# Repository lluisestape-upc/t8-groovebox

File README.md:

# T-8 Groovebox

A 16-step hardware groovebox built around an ESP32-WROOM-32, designed from scratch in KiCad 10. Two copper layers, 290 × 210 mm, DRC-clean and fabrication-ready.

> **Status: designed, not yet fabricated.**
> The layout passes DRC with **0 errors and 0 unconnected nets**, and the Gerber + drill package in [`fab/`](fab/) has been generated and checked. No board has been ordered yet, so nothing here has been measured on real hardware. Every performance figure in this README is a design intent, not a measurement.

---

## What it is

A desktop groovebox in the spirit of the Roland T-8: sixteen step buttons with per-step RGB feedback, ten pots for live parameter control, a rotary encoder for menu navigation, a 2.4" colour display, MIDI in and out over TRS-A, and two independent audio outputs — a line-level I²S DAC and a class-D amplifier for a small onboard speaker. The whole thing is powered and programmed over a single USB-C connector.

The interesting part of this project is not the feature list, it is that the panel layout and most of the routing were **generated and repaired with the KiCad Python API** rather than drawn by hand. See [How the board was built](#how-the-board-was-built).

## Board at a glance

| | |
|---|---|
| Outline | 290.1 × 210.1 mm, with a 7 mm notch for the MIDI jacks |
| Copper layers | 2 (F.Cu / B.Cu), 1 oz |
| Footprints | 104 |
| Pads | 523 |
| Nets | 137 |
| Tracks | 2,570 segments |
| Vias | 1,148 (0.6 mm pad / 0.3 mm drill) |
| Copper zones | 1 GND plane, poured on both layers |
| Min track / clearance | 0.20 mm / 0.20 mm |
| Min drill | 0.30 mm |
| Min copper-to-edge | 0.50 mm |
| Mounting | 6 × M3 (3.2 mm) |
| DRC | 0 errors, 0 unconnected, 12 cosmetic silkscreen warnings |

### Renders

| Top | Bottom |
|---|---|
|  |  |

Vector fabrication views: [top](img/t8_2d_top.svg) · [bottom](img/t8_2d_bottom.svg)

PDFs: [schematic](T8Sequencer_esquematico.pdf) · [PCB](T8Sequencer_pcb.pdf)

---

## Signal chain

```mermaid
flowchart LR
  USB["USB-C J1"] --> UART["CH340C USB-UART"]
  USB --> LDO["AMS1117-3.3"]
  UART -->|UART0| ESP["ESP32-WROOM-32"]
  UART -.->|DTR / RTS via Q1, Q2| ESP
  LDO -->|3.3 V| ESP

  STEPS["16 step buttons"] --> EXP1["MCP23017 0x20"]
  FNKEYS["8 function buttons"] --> EXP2["MCP23017 0x21"]
  EXP1 -->|I2C| ESP
  EXP2 -->|I2C| ESP
  POTS["10 potentiometers"] --> MUX["CD74HC4067 16:1 mux"]
  MUX -->|ADC on GPIO34| ESP
  ENC["Rotary encoder + switch"] --> ESP

  ESP -->|GPIO16| LVL["74AHCT1G125 level shifter"]
  LVL -->|33 ohm series| LEDS["16x WS2812B"]
  ESP -->|SPI| DISP["ST7789 2.4in module"]
  ESP -->|I2S| DAC["I2S DAC header, line out"]
  ESP -->|I2S| AMP["MAX98357A module, speaker"]
  ESP -->|GPIO32| MOUT["MIDI OUT TRS-A, J3"]
  MIDIIN["MIDI IN TRS-A, J2"] --> OPTO["6N138 optocoupler"]
  OPTO -->|GPIO17| ESP
```

---

## Hardware

### Controls and indicators

| Qty | Part | Role |
|---|---|---|
| 16 | 6 mm tact switch | Step buttons (SW1–SW16) |
| 8 | 6 mm tact switch | PLAY, REC, SHIFT, PATT, TEMPO, CLEAR, F1, F2 (SW17–SW24) |
| 10 | Alps RK09K vertical | Parameter pots (RV1–RV10) |
| 1 | Alps EC11E + switch | Menu encoder |
| 16 | WS2812B (PLCC-4, 5×5 mm) | Per-step RGB feedback |
| 1 | ST7789 2.4" module | Display, on an 8-pin 2.54 mm header |

### Active devices

| Ref | Part | Package | Role |
|---|---|---|---|
| U1 | ESP32-WROOM-32 | module | Main MCU |
| U2 | — | 1×06 header | I²S DAC module, line out |
| U3 | ST7789 2.4" | 1×08 header | Display |
| U4 | CD74HC4067M | SOIC-24W | 16:1 analog mux for the pots |
| U5 | AMS1117-3.3 | SOT-223 | 3.3 V linear regulator |
| U6 | CH340C | SOIC-16 | USB to serial |
| U7 | MCP23017 | DIP-28 | I/O expander, step buttons (0x20) |
| U8 | 6N138 | DIP-8 | MIDI IN isolation |
| U9 | MAX98357A | 1×07 header | Class-D amp module, speaker out |
| U10 | MCP23017 | DIP-28 | I/O expander, function buttons (0x21) |
| U11 | 74AHCT1G125 | SOT-23-5 | 3.3 V to 5 V buffer for the LED data line |
| Q1, Q2 | NPN | SOT-23 | Auto-reset (DTR/RTS to EN/IO0) |

### Connectors

| Ref | Connector | Notes |
|---|---|---|
| J1 | USB-C receptacle, USB 2.0 14P | Power + programming, with 5.1 kΩ CC pulldowns |
| J2 | 3.5 mm TRS | MIDI IN, **TRS-A** (tip = DIN 5, ring = DIN 4) |
| J3 | 3.5 mm TRS | MIDI OUT, **TRS-A** |

Audio leaves the board through the connectors on the DAC and amplifier modules, not through board-mounted jacks.

---

## ESP32 pin map

| GPIO | Net | Function |
|---|---|---|
| 0 | `ESP_IO0` | Boot strap, driven by Q2 from RTS |
| 1 / 3 | `TX` / `RX` | UART0 to the CH340C |
| 2 | `DC` | Display data/command |
| 4 | `RES` | Display reset |
| 5 | `TFT_CS` | Display chip select |
| 12 | `MUX_S0` | Mux select bit 0 |
| 13 | `MUX_S1` | Mux select bit 1 |
| 14 | `MUX_S2` | Mux select bit 2 |
| 15 | `DISP_MOSI` | Display data |
| 16 | `LED_DATA` | WS2812B chain, via the 74AHCT1G125 |
| 17 | `MIDI_RX` | MIDI IN, from the 6N138 |
| 18 | `SCL` | I²C clock |
| 19 | `ENC_A` | Encoder channel A |
| 21 | `ENC_B` | Encoder channel B |
| 22 | `I2S_DIN` | I²S data out, shared by both audio devices |
| 23 | `SDA` | I²C data |
| 25 | `I2S_LCK` | I²S word clock |
| 26 | `I2S_BCK` | I²S bit clock |
| 27 | `MUX_S3` | Mux select bit 3 |
| 32 | `MIDI_TX` | MIDI OUT |
| 33 | `DISP_SCK` | Display clock |
| 34 | `MUX_SIG` | Pot mux output to ADC (input-only pin) |
| 35 | `ENC_SW` | Encoder push switch (input-only pin) |
| EN | `ESP_EN` | Reset, driven by Q1 from DTR |

`GPIO34` and `GPIO35` are input-only on the ESP32, which is exactly how they are used here. `GPIO12` is a boot strapping pin (MTDI); it is driven as a mux select with no external pull, so nothing holds it high at reset, but it is worth keeping in mind when writing the firmware.

## I²C and mux map

Both expanders share `SDA`/`SCL` with `RESET` tied to 3.3 V. Buttons pull to ground, so enable the internal pull-ups (`GPPU`).

| Device | Address | Port A | Port B |
|---|---|---|---|
| U7 | `0x20` | steps 1–8 | steps 9–16 |
| U10 | `0x21` | PLAY, REC, SHIFT, PATT, TEMPO, CLEAR, F1, F2 | free (8 spare inputs) |

The CD74HC4067 uses 10 of its 16 channels (`POT0`–`POT9`), selected by `MUX_S0..S3`, with the common pin read on `GPIO34`. Allow for RC settling between the channel switch and the ADC read.

The WS2812B chain is wired as a serpentine, not in reference order:

```
D1 → D2 → D3 → D4 → D5 → D10 → D11 → D12 → D6 → D7 → D8 → D9 → D14 → D15 → D16 → D17
```

Firmware has to map logical step *n* onto this physical order.

---

## Fabrication

[`fab/`](fab/) holds the complete package, also zipped as [`T8Sequencer_fab.zip`](T8Sequencer_fab.zip):

- 7 Gerbers — F.Cu, B.Cu, F.Mask, B.Mask, F.Silkscreen, B.Silkscreen, Edge.Cuts
- Excellon drill files, split PTH / NPTH
- `.gbrjob` job file

Settings the design was checked against:

| Setting | Value | Why |
|---|---|---|
| Layers | 2 | |
| Thickness | 1.6 mm | |
| Copper weight | 1 oz | 2 oz would raise the headroom of the 0.2 mm tracks from ≈0.74 A to ≈1.2 A, at higher cost |
| Min hole size | **0.3 mm** | 0.2 mm crosses into a much more expensive price tier |
| Min track / spacing | 0.2 mm / 0.2 mm | |
| Surface finish | HASL | |

The ESP32 thermal vias were deliberately enlarged from 0.2 mm to 0.3 mm drill (0.7 mm pad) purely to stay under the cheaper drill tier.

---

## Repository layout

```
T8Sequencer.kicad_pro          project
T8Sequencer.kicad_sch          schematic (single sheet)
T8Sequencer.kicad_pcb          layout
T8Sequencer.xml                netlist export
fp-lib-table                   project footprint libraries
sin_marco.kicad_wks            borderless worksheet, for clean plots
lib/Lluis.kicad_sym            custom symbols (module headers)
Lluis.pretty/                  custom footprints
LCD ST7789V.pretty/            the original FPC display footprint (superseded)
fab/                           Gerbers + drill
img/                           3D renders and 2D fabrication views
build_pcb.py                   board bring-up script
place_panel.py                 panel placement generator
scripts_arreglo/               the repair scripts, in the order they were run
```

### Opening the project

The schematic depends on the custom symbol library in `lib/Lluis.kicad_sym`, which is **not** registered by a project-level `sym-lib-table`. Add it once under *Preferences → Manage Symbol Libraries* with the nickname `Lluis`, or point an existing entry at the copy in `lib/`. The footprint libraries resolve automatically through `fp-lib-table`.

---

## How the board was built

The panel is a grid of 16 switches, 16 LEDs and 10 pots. Placing that by hand is tedious and error-prone, so the geometry is generated instead:

- **`place_panel.py`** computes the panel grid and writes footprint positions straight into the board.
- **`build_pcb.py`** handles board-level bring-up.
- **`scripts_arreglo/`** holds the repair passes in the order they were run — `fix1`–`fix9`, `fix11`, `fix12` for connectivity and geometry, `ruta`–`ruta4` for routing, `esq` for the schematic. Each one is a single, auditable change.

Two problems in there are worth reading if you ever script KiCad.

**Duplicate-numbered pads.** 73 pads in this design share a number with another pad in the same footprint — tact switches with two pads numbered 1 and two numbered 2, the USB-C shield with four `SH` pads, the ESP32 thermal pad split into eight. The netlist assigns a net to *one* of them, so the rest stay at net 0 and the copper never connects. Neither ERC nor the netlist reveals this. The fix walks every footprint, groups pads by number, and propagates the single non-zero net to its twins:

```python
byn = collections.defaultdict(list)
for p in f.Pads():
    byn[p.GetNumber()].append(p)
for num, ps in byn.items():
    nets = {p.GetNetCode() for p in ps if p.GetNetCode() != 0}
    if len(nets) == 1 and any(p.GetNetCode() == 0 for p in ps):
        net = B.FindNet(nets.pop())
        for p in ps:
            if p.GetNetCode() == 0:
                p.SetNet(net)
```

**`GetTracks()` is invalidated by `Remove()`.** Iterating the track list while deleting from it segfaults the interpreter. Collect first, delete afterwards:

```python
fuera = [t for t in B.GetTracks() if condicion(t)]
for t in fuera:
    B.Remove(t)
```

---

## Design notes and open risks

Written down plainly, because none of it has been measured yet.

**The 3.3 V regulator is the hot spot.** The AMS1117 drops 5 V to 3.3 V linearly, so it burns 1.7 V times whatever the rail draws:

| 3.3 V load | Dissipation | Rise over ambient (SOT-223) |
|---|---|---|
| 300 mA | 0.51 W | ≈40 °C |
| 500 mA | 0.85 W | ≈65 °C |
| 800 mA | 1.36 W | too much |

Quiescent operation is fine. With Wi-Fi transmitting (peaks around 500 mA) plus the display backlight, the package gets hot. This is the first thing to measure on a real board, and the obvious upgrade is a buck converter.

**The LED ring can outdraw a USB port.** 16 WS2812B at full white is roughly 960 mA on the 5 V rail, against the 500 mA a plain USB 2.0 port guarantees. Cap the brightness in firmware.

**Every track sits at the 0.2 mm minimum.** That is ≈0.74 A at 1 oz by IPC-2221 — adequate for the logic rails, with no margin on the 5 V LED rail. Widening the power tracks was attempted and produced 138+ clearance errors: the routing is dense enough that it needs manual rework, or 2 oz copper, or both.

**Three module pinouts are assumed, not verified.** The display (U3), the DAC (U2) and the amplifier (U9) are all 2.54 mm headers, and the pin order was taken from the common breakout variants. **Check the silkscreen on the parts you actually buy against the schematic before soldering.** The schematic carries a note to this effect on U9.

**12 silkscreen warnings remain.** Reference text on J2 and J3 overhangs the board edge near the MIDI notch. Cosmetic only, no effect on fabrication.

---

## Next steps

- [ ] Order the boards (1 oz, min hole 0.3 mm)
- [ ] Buy the 8-pin 2.4" ST7789 module and verify its pin order
- [ ] Verify the MAX98357A and I²S DAC module pinouts
- [ ] Prototype the firmware in simulation before the boards arrive
- [ ] Bring-up: power rails, regulator temperature, USB enumeration, auto-reset
- [ ] Characterise: line-out THD+N and noise floor, I²S end-to-end latency, MIDI TRS jitter, LED current against brightness
- [ ] Add silkscreen function labels for the pots and step buttons

---

## License

MIT — see [LICENSE](LICENSE).

Designed by [Lluís Estapé](https://github.com/lluisestape-upc). KiCad 10.0.1.

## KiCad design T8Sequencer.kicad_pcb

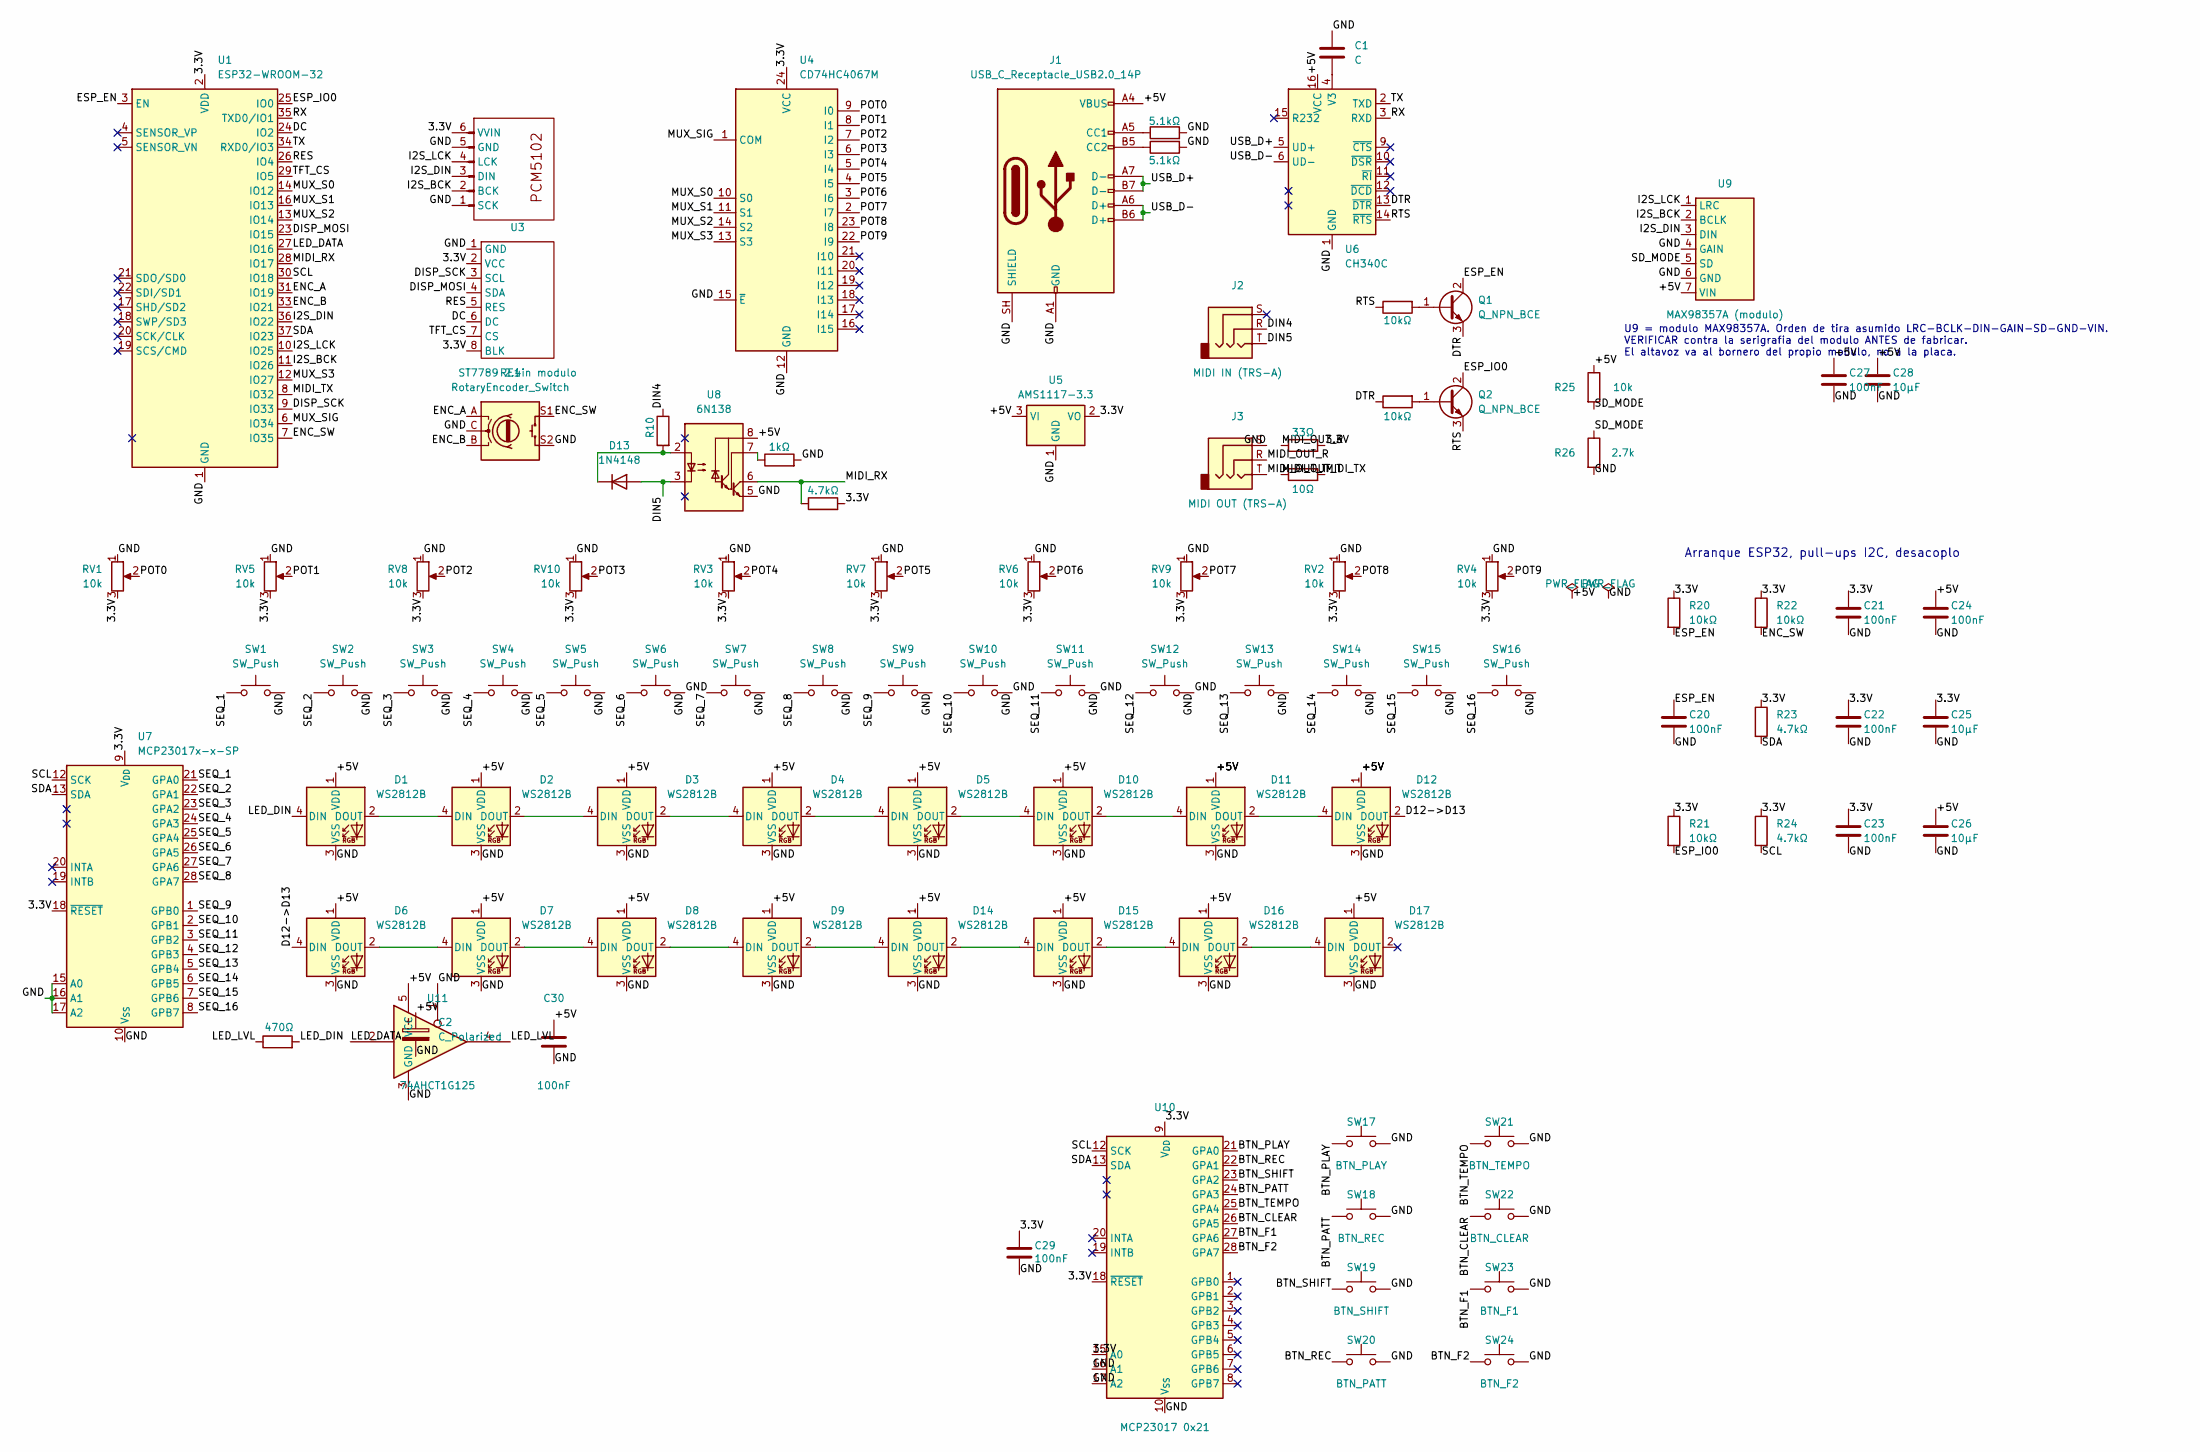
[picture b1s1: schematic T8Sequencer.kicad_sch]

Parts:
C1: C; C_0805_2012Metric
C2: C_Polarized; CP_Radial_D10.0mm_P5.00mm
C20, C21, C22, C23, C24, C27, C29, C30: 100nF; C_0805_2012Metric
C25, C26, C28: 10µF; C_0805_2012Metric
D1, D2, D3, D4, D5, D6, D7, D8, D9, D10, D11, D12, D14, D15, D16, D17: WS2812B; LED_WS2812B_PLCC4_5.0x5.0mm_P3.2mm
D13: 1N4148; D_DO-35_SOD27_P7.62mm_Horizontal
J1: USB_C_Receptacle_USB2.0_14P; USB_C_Receptacle_HRO_TYPE-C-31-M-12
J2: MIDI IN (TRS-A); Jack_3.5mm_CUI_SJ1-3523N_Horizontal
J3: MIDI OUT (TRS-A); Jack_3.5mm_CUI_SJ1-3523N_Horizontal
Q1, Q2: Q_NPN_BCE; SOT-23
R1, R2: 5.1kΩ; R_0805_2012Metric
R3, R4, R20, R21, R22: 10kΩ; R_0805_2012Metric
R5: 470Ω; R_0805_2012Metric
R6: 1kΩ; R_0805_2012Metric
R7, R23, R24: 4.7kΩ; R_0805_2012Metric
R8: 33Ω; R_0805_2012Metric
R9: 10Ω; R_0805_2012Metric
R10: 220; R_0805_2012Metric
R25: 10k; R_0805_2012Metric
R26: 2.7k; R_0805_2012Metric
RE1: RotaryEncoder_Switch; RotaryEncoder_Alps_EC11E-Switch_Vertical_H20mm
RV1, RV2, RV3, RV4, RV5, RV6, RV7, RV8, RV9, RV10: 10k; Potentiometer_Alps_RK09K_Single_Vertical
SW1, SW2, SW3, SW4, SW5, SW6, SW7, SW8, SW9, SW10, SW11, SW12, SW13, SW14, SW15, SW16: SW_Push; SW_PUSH_6mm
SW17: BTN_PLAY; SW_PUSH_6mm
SW18: BTN_REC; SW_PUSH_6mm
SW19: BTN_SHIFT; SW_PUSH_6mm
SW20: BTN_PATT; SW_PUSH_6mm
SW21: BTN_TEMPO; SW_PUSH_6mm
SW22: BTN_CLEAR; SW_PUSH_6mm
SW23: BTN_F1; SW_PUSH_6mm
SW24: BTN_F2; SW_PUSH_6mm
U1: ESP32-WROOM-32
U2: PinHeader_1x06_P2.54mm_Vertical
U3: ST7789 2.4in modulo; PinHeader_1x08_P2.54mm_Vertical
U4: CD74HC4067M; SOIC-24W_7.5x15.4mm_P1.27mm
U5: AMS1117-3.3; SOT-223-3_TabPin2
U6: CH340C; SOIC-16_3.9x9.9mm_P1.27mm
U7: MCP23017x-x-SP; DIP-28_W7.62mm
U8: 6N138; DIP-8_W7.62mm
U9: MAX98357A (modulo); PinHeader_1x07_P2.54mm_Vertical
U10: MCP23017 0x21; DIP-28_W7.62mm
U11: 74AHCT1G125; SOT-23-5

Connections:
/3.3V: C21.1, C22.1, C23.1, C25.1, C29.1, R7.2, R8.2, R20.1, R21.1, R22.1, R23.1, R24.1, RV1.3, RV2.3, RV3.3, RV4.3, RV5.3, RV6.3, RV7.3, RV8.3, RV9.3, RV10.3, U1.2 (VDD), U2.6 (VVIN), U3.2 (VCC), U3.8 (BLK), U4.24 (VCC), U5.2 (VO), U7.9 (V_{DD}), U7.18 (~RESET), U10.9 (V_{DD}), U10.15 (A0), U10.18 (~RESET)
/+5V: C2.1, C24.1, C26.1, C27.1, C28.1, C30.1, D1.1 (VDD), D2.1 (VDD), D3.1 (VDD), D4.1 (VDD), D5.1 (VDD), D6.1 (VDD), D7.1 (VDD), D8.1 (VDD), D9.1 (VDD), D10.1 (VDD), D11.1 (VDD), D12.1 (VDD), D14.1 (VDD), D15.1 (VDD), D16.1 (VDD), D17.1 (VDD), J1.A4 (VBUS), J1.A9 (VBUS), J1.B4 (VBUS), J1.B9 (VBUS), R25.1, U5.3 (VI), U6.16 (VCC), U8.8 (VCC), U9.7 (VIN), U11.5 (VCC)
/BTN_CLEAR: SW22.1, U10.26 (GPA5)
/BTN_F1: SW23.1, U10.27 (GPA6)
/BTN_F2: SW24.1, U10.28 (GPA7)
/BTN_PATT: SW18.1, U10.24 (GPA3)
/BTN_PLAY: SW17.1, U10.21 (GPA0)
/BTN_REC: SW20.1, U10.22 (GPA1)
/BTN_SHIFT: SW19.1, U10.23 (GPA2)
/BTN_TEMPO: SW21.1, U10.25 (GPA4)
/D12->D13: D6.4 (DIN), D12.2 (DOUT)
/DC: U1.24 (IO2), U3.6 (DC)
/DIN4: J2.R, R10.1
/DIN5: D13.2 (A), J2.T, U8.3 (C2)
/DISP_MOSI: U1.23 (IO15), U3.4 (SDA)
/DISP_SCK: U1.9 (IO33), U3.3 (SCL)
/DTR: Q1.3 (E), R4.1, U6.13 (~DTR)
/ENC_A: RE1.A, U1.31 (IO19)
/ENC_B: RE1.B, U1.33 (IO21)
/ENC_SW: R22.2, RE1.S1, U1.7 (IO35)
/ESP_EN: C20.1, Q1.2 (C), R20.2, U1.3 (EN)
/ESP_IO0: Q2.2 (C), R21.2, U1.25 (IO0)
/GND: C1.1, C2.2, C20.2, C21.2, C22.2, C23.2, C24.2, C25.2, C26.2, C27.2, C28.2, C29.2, C30.2, D1.3 (VSS), D2.3 (VSS), D3.3 (VSS), D4.3 (VSS), D5.3 (VSS), D6.3 (VSS), D7.3 (VSS), D8.3 (VSS), D9.3 (VSS), D10.3 (VSS), D11.3 (VSS), D12.3 (VSS), D14.3 (VSS), D15.3 (VSS), D16.3 (VSS), D17.3 (VSS), J1.A1 (GND), J1.A8, J1.A12 (GND), J1.B1 (GND), J1.B8, J1.B12 (GND), J1.SH (SHIELD), J3.S, R1.2, R2.2, R6.2, R26.2, RE1.C, RE1.S2, RV1.1, RV2.1, RV3.1, RV4.1, RV5.1, RV6.1, RV7.1, RV8.1, RV9.1, RV10.1, SW1.2, SW2.2, SW3.2, SW4.2, SW5.2, SW6.2, SW7.2, SW8.2, SW9.2, SW10.2, SW11.2, SW12.2, SW13.2, SW14.2, SW15.2, SW16.2, SW17.2, SW18.2, SW19.2, SW20.2, SW21.2, SW22.2, SW23.2, SW24.2, U1.1 (GND), U1.15 (GND), U1.38 (GND), U1.39 (GND), U2.1 (SCK), U2.5 (GND), U3.1 (GND), U4.12 (GND), U4.15 (~E), U5.1 (GND), U6.1 (GND), U7.10 (V_{SS}), U7.15 (A0), U7.16 (A1), U7.17 (A2), U8.5 (GND), U9.4 (GAIN), U9.6 (GND), U10.10 (V_{SS}), U10.16 (A1), U10.17 (A2), U11.1, U11.3 (GND)
/I2S_BCK: U1.11 (IO26), U2.2 (BCK), U9.2 (BCLK)
/I2S_DIN: U1.36 (IO22), U2.3 (DIN), U9.3 (DIN)
/I2S_LCK: U1.10 (IO25), U2.4 (LCK), U9.1 (LRC)
/LED_DATA: U1.27 (IO16), U11.2
/LED_DIN: D1.4 (DIN), R5.2
/LED_LVL: R5.1, U11.4
/MIDI_OUT_R: J3.R, R8.1
/MIDI_OUT_T: J3.T, R9.1
/MIDI_RX: R7.1, U1.28 (IO17), U8.6 (VO2)
/MIDI_TX: R9.2, U1.8 (IO32)
/MUX_S0: U1.14 (IO12), U4.10 (S0)
/MUX_S1: U1.16 (IO13), U4.11 (S1)
/MUX_S2: U1.13 (IO14), U4.14 (S2)
/MUX_S3: U1.12 (IO27), U4.13 (S3)
/MUX_SIG: U1.6 (IO34), U4.1 (COM)
/POT0: RV1.2, U4.9 (I0)
/POT1: RV5.2, U4.8 (I1)
/POT2: RV8.2, U4.7 (I2)
/POT3: RV10.2, U4.6 (I3)
/POT4: RV3.2, U4.5 (I4)
/POT5: RV7.2, U4.4 (I5)
/POT6: RV6.2, U4.3 (I6)
/POT7: RV9.2, U4.2 (I7)
/POT8: RV2.2, U4.23 (I8)
/POT9: RV4.2, U4.22 (I9)
/RES: U1.26 (IO4), U3.5 (RES)
/RTS: Q2.3 (E), R3.1, U6.14 (~RTS)
/RX: U1.35 (TXD0/IO1), U6.3 (RXD)
/SCL: R24.2, U1.30 (IO18), U7.12 (SCK), U10.12 (SCK)
/SDA: R23.2, U1.37 (IO23), U7.13 (SDA), U10.13 (SDA)
/SD_MODE: R25.2, R26.1, U9.5 (SD)
/SEQ_1: SW1.1, U7.21 (GPA0)
/SEQ_2: SW2.1, U7.22 (GPA1)
/SEQ_3: SW3.1, U7.23 (GPA2)
/SEQ_4: SW4.1, U7.24 (GPA3)
/SEQ_5: SW5.1, U7.25 (GPA4)
/SEQ_6: SW6.1, U7.26 (GPA5)
/SEQ_7: SW7.1, U7.27 (GPA6)
/SEQ_8: SW8.1, U7.28 (GPA7)
/SEQ_9: SW9.1, U7.1 (GPB0)
/SEQ_10: SW10.1, U7.2 (GPB1)
/SEQ_11: SW11.1, U7.3 (GPB2)
/SEQ_12: SW12.1, U7.4 (GPB3)
/SEQ_13: SW13.1, U7.5 (GPB4)
/SEQ_14: SW14.1, U7.6 (GPB5)
/SEQ_15: SW15.1, U7.7 (GPB6)
/SEQ_16: SW16.1, U7.8 (GPB7)
/TFT_CS: U1.29 (IO5), U3.7 (CS)
/TX: U1.34 (RXD0/IO3), U6.2 (TXD)
/USB_D+: J1.A7 (D-), J1.B7 (D-), U6.5 (UD+)
/USB_D-: J1.A6 (D+), J1.B6 (D+), U6.6 (UD-)
unnamed: D1.2 (DOUT), D2.4 (DIN)
unnamed: D2.2 (DOUT), D3.4 (DIN)
unnamed: D3.2 (DOUT), D4.4 (DIN)
unnamed: D4.2 (DOUT), D5.4 (DIN)
unnamed: D6.2 (DOUT), D7.4 (DIN)
unnamed: D7.2 (DOUT), D8.4 (DIN)
unnamed: D8.2 (DOUT), D9.4 (DIN)
unnamed: D5.2 (DOUT), D10.4 (DIN)
unnamed: D10.2 (DOUT), D11.4 (DIN)
unnamed: D11.2 (DOUT), D12.4 (DIN)
unnamed: D13.1 (K), R10.2, U8.2 (C1)
unnamed: D9.2 (DOUT), D14.4 (DIN)
unnamed: D14.2 (DOUT), D15.4 (DIN)
unnamed: D15.2 (DOUT), D16.4 (DIN)
unnamed: D16.2 (DOUT), D17.4 (DIN)
unnamed: J1.A5 (CC1), R1.1
unnamed: J1.B5 (CC2), R2.1
unnamed: Q1.1 (B), R3.2
unnamed: Q2.1 (B), R4.2
unnamed: C1.2, U6.4 (V3)
unnamed: R6.1, U8.7 (VO1)

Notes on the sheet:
Arranque ESP32, pull-ups I2C, desacoplo
U9 = modulo MAX98357A. Orden de tira asumido LRC-BCLK-DIN-GAIN-SD-GND-VIN. VERIFICAR contra la serigrafia del modulo ANTES de fabricar. El altavoz va al bornero del propio modulo, no a la placa.

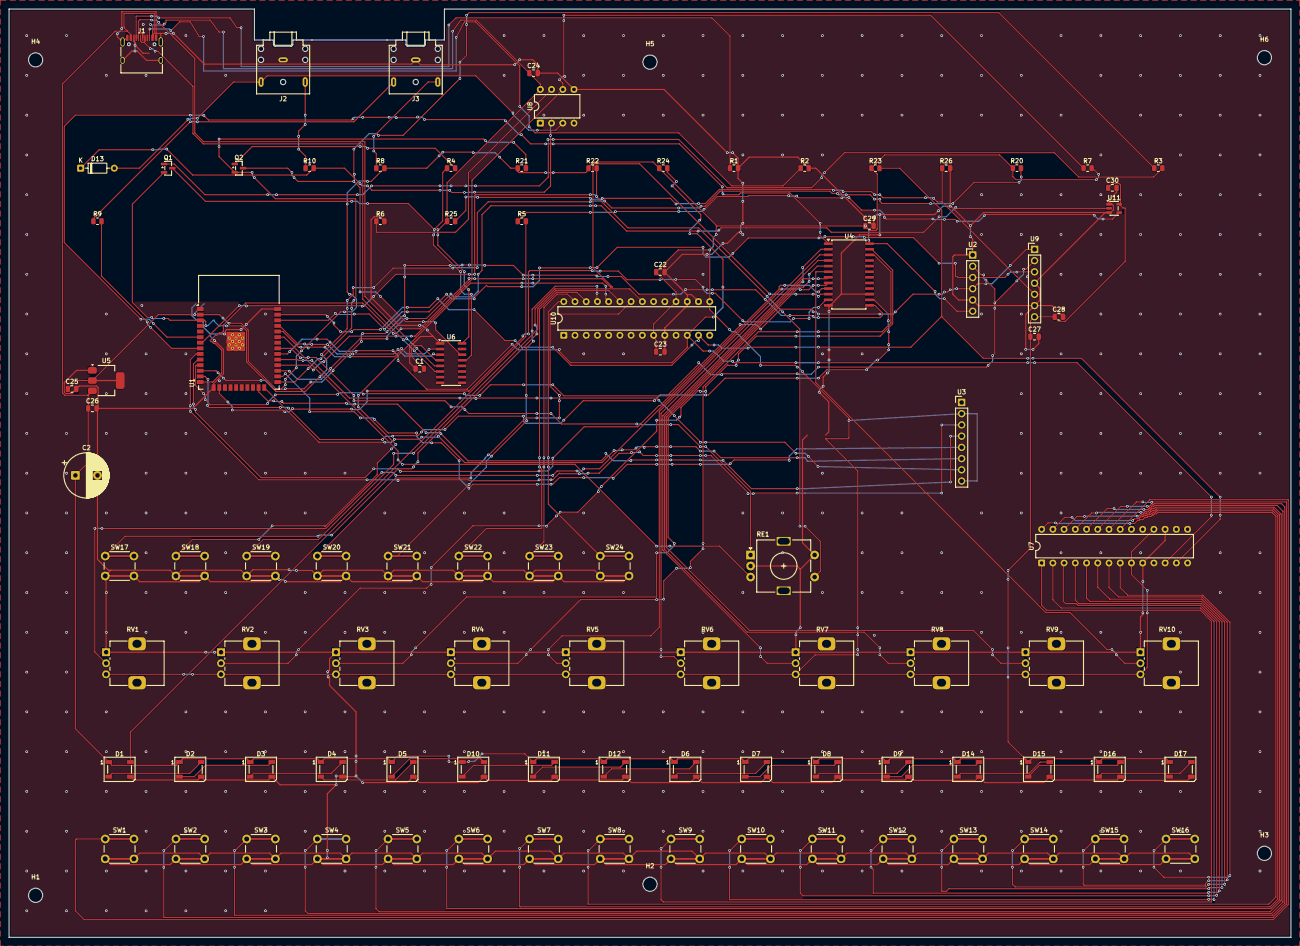
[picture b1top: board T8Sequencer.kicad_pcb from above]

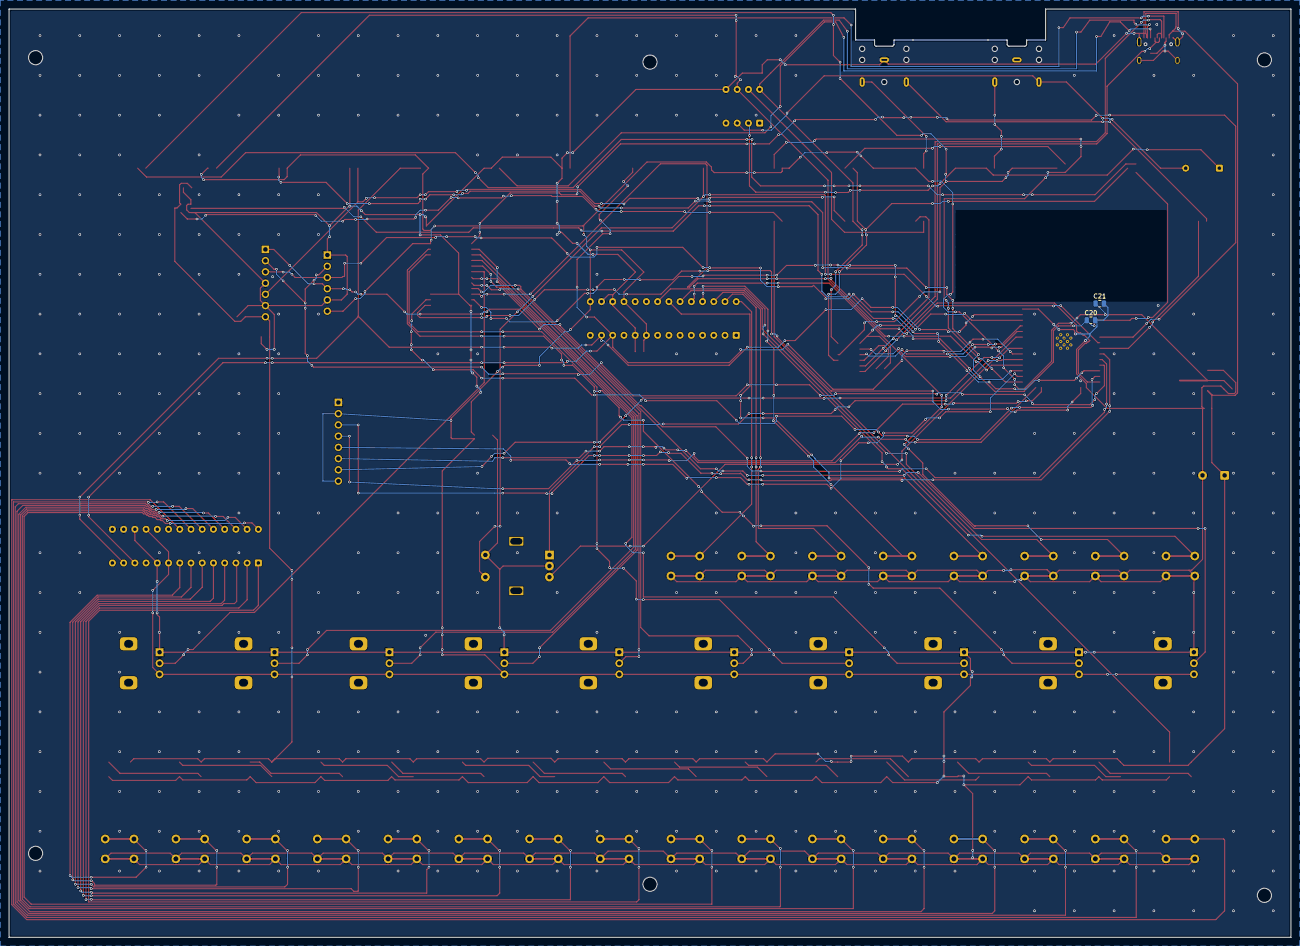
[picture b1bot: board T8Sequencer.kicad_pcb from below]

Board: 2 copper layers, 290.0 x 210.0 mm, 104 parts (2 on the bottom side), 95 nets.

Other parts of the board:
H1, H2, H3, H4, H5, H6: MountingHole_3.2mm_M3

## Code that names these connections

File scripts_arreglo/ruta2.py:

# -*- coding: utf-8 -*-
import pcbnew
B = pcbnew.LoadBoard("T8Sequencer.kicad_pcb")
FM, TM = pcbnew.FromMM, pcbnew.ToMM
def V(x,y): return pcbnew.VECTOR2I(FM(x), FM(y))
F, Bo = pcbnew.F_Cu, pcbnew.B_Cu
def cerca(p,x,y,tol=0.03): return abs(TM(p.x)-x)<tol and abs(TM(p.y)-y)<tol

# --- borrar el intento anterior y los ramales muertos del display -----------
BORRA = [("/DISP_SCK",191.35,109.50,215.50,94.08),
         ("/DISP_MOSI",184.50,98.80,191.00,105.30),
         ("/DISP_MOSI",191.00,105.30,191.00,109.00),
         ("/DISP_SCK",191.60,104.67,184.93,98.00),
         ("/DISP_SCK",191.60,109.50,191.60,104.67)]
fuera=[]
for t in B.GetTracks():
    if t.GetClass()=="PCB_VIA":
        if t.GetNetname()=="/DISP_SCK" and cerca(t.GetPosition(),191.35,109.50): fuera.append(t)
        continue
    for n,x1,y1,x2,y2 in BORRA:
        if t.GetNetname()!=n: continue
        a,b=t.GetStart(),t.GetEnd()
        if (cerca(a,x1,y1) and cerca(b,x2,y2)) or (cerca(a,x2,y2) and cerca(b,x1,y1)):
            fuera.append(t); break
print("elementos retirados (intento previo + ramales muertos):", len(fuera))
for t in fuera: B.Remove(t)

# --- rutado definitivo --------------------------------------------------------
def trk(x1,y1,x2,y2,layer,net,w=0.2):
    t=pcbnew.PCB_TRACK(B); t.SetStart(V(x1,y1)); t.SetEnd(V(x2,y2))
    t.SetLayer(layer); t.SetWidth(FM(w)); t.SetNet(B.FindNet(net)); B.Add(t)
def via(x,y,net):
    v=pcbnew.PCB_VIA(B); v.SetPosition(V(x,y)); v.SetViaType(pcbnew.VIATYPE_THROUGH)
    v.SetLayerPair(F,Bo); v.SetDrill(FM(0.3))
    try: v.SetWidth(FM(0.6))
    except TypeError: v.SetWidth(F,FM(0.6))
    v.SetNet(B.FindNet(net)); B.Add(v)

# RES y DC: recta por la cara inferior, no se cruzan con nadie
trk(180.10, 99.50, 215.50, 99.16, Bo, "/RES");   print("  /RES      -> pin 5, recta por B.Cu")
trk(180.10,101.50, 215.50,101.70, Bo, "/DC");    print("  /DC       -> pin 6, recta por B.Cu")

# CS: salta por arriba a la cara superior para pasar por debajo de DC
trk(180.84,101.18, 182.50,103.00, F,  "/TFT_CS"); via(182.50,103.00,"/TFT_CS")
trk(182.50,103.00, 215.50,104.24, Bo, "/TFT_CS"); print("  /TFT_CS   -> pin 7, esquiva a DC")

# MOSI: sale del bus de y=109, cruza por B.Cu y sube por F.Cu en x=213
trk(191.00,109.00, 193.00,107.00, F,  "/DISP_MOSI"); via(193.00,107.00,"/DISP_MOSI")
trk(193.00,107.00, 213.00,107.00, Bo, "/DISP_MOSI"); via(213.00,107.00,"/DISP_MOSI")
trk(213.00,107.00, 213.00, 96.62, F,  "/DISP_MOSI"); via(213.00, 96.62,"/DISP_MOSI")
trk(213.00, 96.62, 215.50, 96.62, Bo, "/DISP_MOSI"); print("  /DISP_MOSI-> pin 4, sube por x=213")

# SCK: igual pero subiendo por x=211
trk(191.60,109.50, 194.50,109.50, F,  "/DISP_SCK"); via(194.50,109.50,"/DISP_SCK")
trk(194.50,109.50, 211.00,109.50, Bo, "/DISP_SCK"); via(211.00,109.50,"/DISP_SCK")
trk(211.00,109.50, 211.00, 94.08, F,  "/DISP_SCK"); via(211.00, 94.08,"/DISP_SCK")
trk(211.00, 94.08, 215.50, 94.08, Bo, "/DISP_SCK"); print("  /DISP_SCK -> pin 3, sube por x=211")

pcbnew.ZONE_FILLER(B).Fill(B.Zones())
B.Save("T8Sequencer.kicad_pcb")
print("guardado")
